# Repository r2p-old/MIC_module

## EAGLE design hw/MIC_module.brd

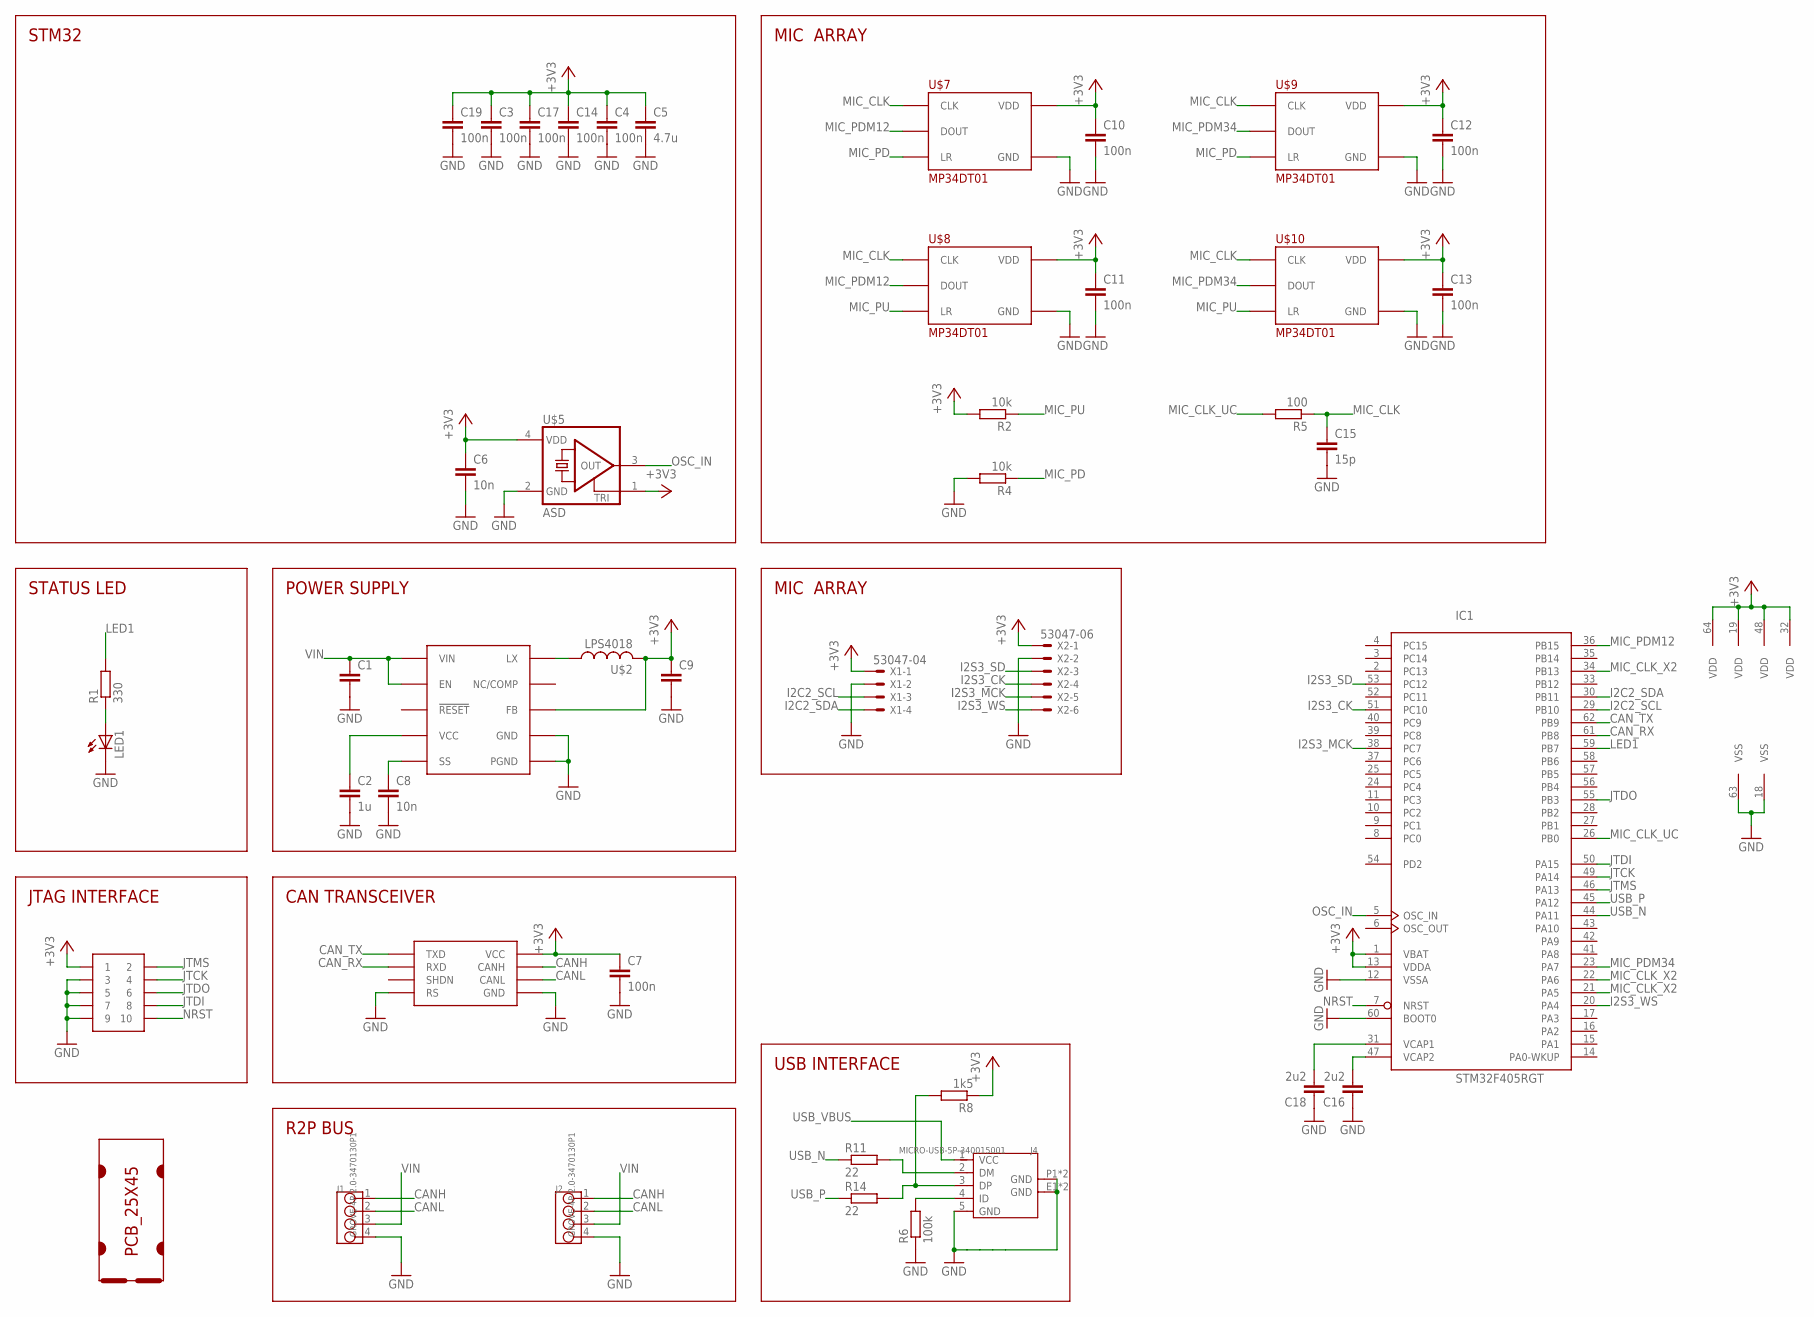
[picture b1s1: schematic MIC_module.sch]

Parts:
C1: C-EUC1206; C1206
C2: 1u; C0603
C3, C4, C7, C10, C11, C12, C13, C14, C17, C19: 100n; C0603
C5: 4.7u; C0805
C6, C8: 10n; C0603
C9: C-EUC0805; C0805
C15: 15p; C0603
C16, C18: 2u2; C0603
IC1: STM32F405RGT; LQFP64
J1, J2: GROVE-4P-2.0-3470130P1; 4P-2.0
J4: MICRO-USB-5P-340015001; B-SMD-5P
LED1: LEDCHIPLED_0805; CHIPLED_0805
R1: 330; R0603
R2, R4: 10k; R0603
R5: 100; R0603
R6: 100k; R0603
R8: 1k5; R0603
R11, R14: 22; R0603
SOT1: MAX3051EKA; SOT23-8L
U$1: PCB_25X45; 25X45
U$2: LPS4018
U$3: MAX17501; TDFN-10
U$4: JTAG-TH; SAMTEC_FTSH-105-TH
U$5: ASD; 2.5X2
U$7, U$8, U$9, U$10: MP34DT01
X1: 53047-04
X2: 53047-06

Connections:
+3V3: C3.1, C4.1, C5.1, C6.1, C7.1, C9.1, C10.1, C11.1, C12.1, C13.1, C14.1, C17.1, C19.1, IC1.1 (VBAT), IC1.13 (VDDA), IC1.19 (VDD), IC1.32 (VDD), IC1.48 (VDD), IC1.64 (VDD), R2.2, R8.1, SOT1.3 (VCC), U$2.P$2 (2), U$3.P$5 (FB), U$4.1, U$5.1 (TRI), U$5.4 (VDD), U$7.P$1 (VDD), U$8.P$1 (VDD), U$9.P$1 (VDD), U$10.P$1 (VDD), X1.1, X2.1
CANH: J1.1, J2.1, SOT1.7 (CANH)
CANL: J1.2, J2.2, SOT1.6 (CANL)
CAN_RX: IC1.61 (PB8), SOT1.4 (RXD)
CAN_TX: IC1.62 (PB9), SOT1.1 (TXD)
GND: C1.2, C2.2, C3.2, C4.2, C5.2, C6.2, C7.2, C8.2, C9.2, C10.2, C11.2, C12.2, C13.2, C14.2, C15.2, C16.1, C17.2, C18.1, C19.2, IC1.12 (VSSA), IC1.18 (VSS), IC1.60 (BOOT0), IC1.63 (VSS), J1.4, J2.4, J4.5 (GND), J4.E1 (GND), J4.E2 (GND), J4.P1 (GND), J4.P2 (GND), LED1.C, R4.2, R6.1, SOT1.2 (GND), SOT1.8 (RS), U$3.P$1 (PGND), U$3.P$9 (GND), U$3.P$11 (PGND), U$4.3, U$4.5, U$4.7, U$4.9, U$5.2 (GND), U$7.P$5 (GND), U$7.P$6 (GND), U$7.P$7 (GND), U$7.P$8 (GND), U$8.P$5 (GND), U$8.P$6 (GND), U$8.P$7 (GND), U$8.P$8 (GND), U$9.P$5 (GND), U$9.P$6 (GND), U$9.P$7 (GND), U$9.P$8 (GND), U$10.P$5 (GND), U$10.P$6 (GND), U$10.P$7 (GND), U$10.P$8 (GND), X1.2, X2.2
I2C2_SCL: IC1.29 (PB10), X1.3
I2C2_SDA: IC1.30 (PB11), X1.4
I2S3_CK: IC1.51 (PC10), X2.4
I2S3_MCK: IC1.38 (PC7), X2.5
I2S3_SD: IC1.53 (PC12), X2.3
I2S3_WS: IC1.20 (PA4), X2.6
JTCK: IC1.49 (PA14), U$4.4
JTDI: IC1.50 (PA15), U$4.8
JTDO: IC1.55 (PB3), U$4.6
JTMS: IC1.46 (PA13), U$4.2
LED1: IC1.59 (PB7), R1.2
MIC_CLK: C15.1, R5.1, U$7.P$3 (CLK), U$8.P$3 (CLK), U$9.P$3 (CLK), U$10.P$3 (CLK)
MIC_CLK_UC: IC1.26 (PB0), R5.2
MIC_CLK_X2: IC1.21 (PA5), IC1.22 (PA6), IC1.34 (PB13)
MIC_PD: R4.1, U$7.P$2 (LR), U$9.P$2 (LR)
MIC_PDM12: IC1.36 (PB15), U$7.P$4 (DOUT), U$8.P$4 (DOUT)
MIC_PDM34: IC1.23 (PA7), U$9.P$4 (DOUT), U$10.P$4 (DOUT)
MIC_PU: R2.1, U$8.P$2 (LR), U$10.P$2 (LR)
unnamed: U$2.P$1 (1), U$3.P$10 (LX)
unnamed: J4.2 (DM), R11.2
unnamed: LED1.A, R1.1
unnamed: J4.4 (ID), R6.2
unnamed: C16.2, IC1.47 (VCAP2)
unnamed: C2.1, U$3.P$4 (VCC)
unnamed: C8.1, U$3.P$6 (SS)
unnamed: C18.2, IC1.31 (VCAP1)
unnamed: J4.3 (DP), R8.2, R14.2
NRST: IC1.7 (NRST), U$4.10
OSC_IN: IC1.5 (OSC_IN), U$5.3 (OUT)
USB_N: IC1.44 (PA11), R11.1
USB_P: IC1.45 (PA12), R14.1
USB_VBUS: J4.1 (VCC)
VIN: C1.1, J1.3, J2.3, U$3.P$2 (VIN), U$3.P$3 (EN)

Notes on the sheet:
STM32
STATUS LED
JTAG INTERFACE
POWER SUPPLY
CAN TRANSCEIVER
R2P BUS
USB INTERFACE
MIC ARRAY

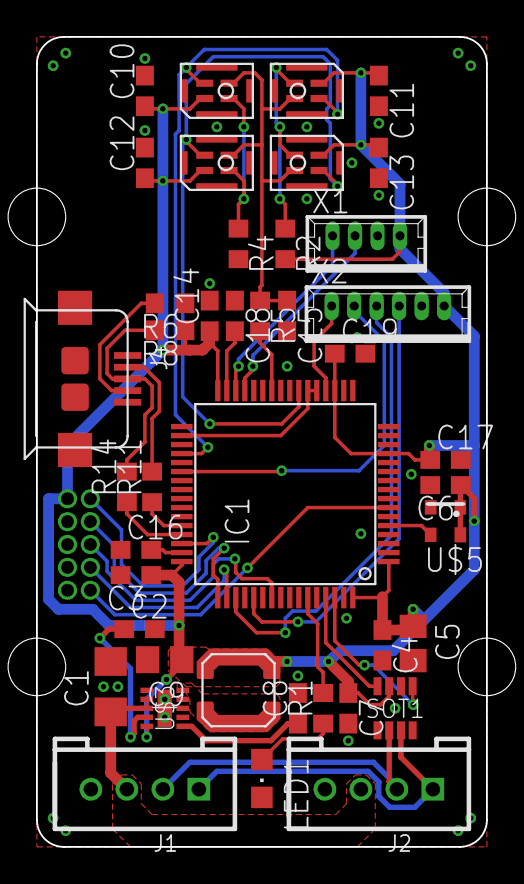
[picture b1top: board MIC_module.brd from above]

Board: 2 copper layers, 25.0 x 45.0 mm, 44 parts (0 on the bottom side), 38 nets.

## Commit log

2014-12-08 layout completed
2014-12-12 added Makefile
2014-12-16 layout in progress
2014-12-16 small fixes for production
2015-01-07 DRC ok
2015-01-07 added USB port
2015-01-28 fixed led polarity
2015-02-19 Fixed directory creation
2015-02-19 Fixed silkscreen
